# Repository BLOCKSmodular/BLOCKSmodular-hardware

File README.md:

# BLOCKSmodular-hardware
**WORK IN PROGRESS**  
This is work in progress. Please use it at your own risk.

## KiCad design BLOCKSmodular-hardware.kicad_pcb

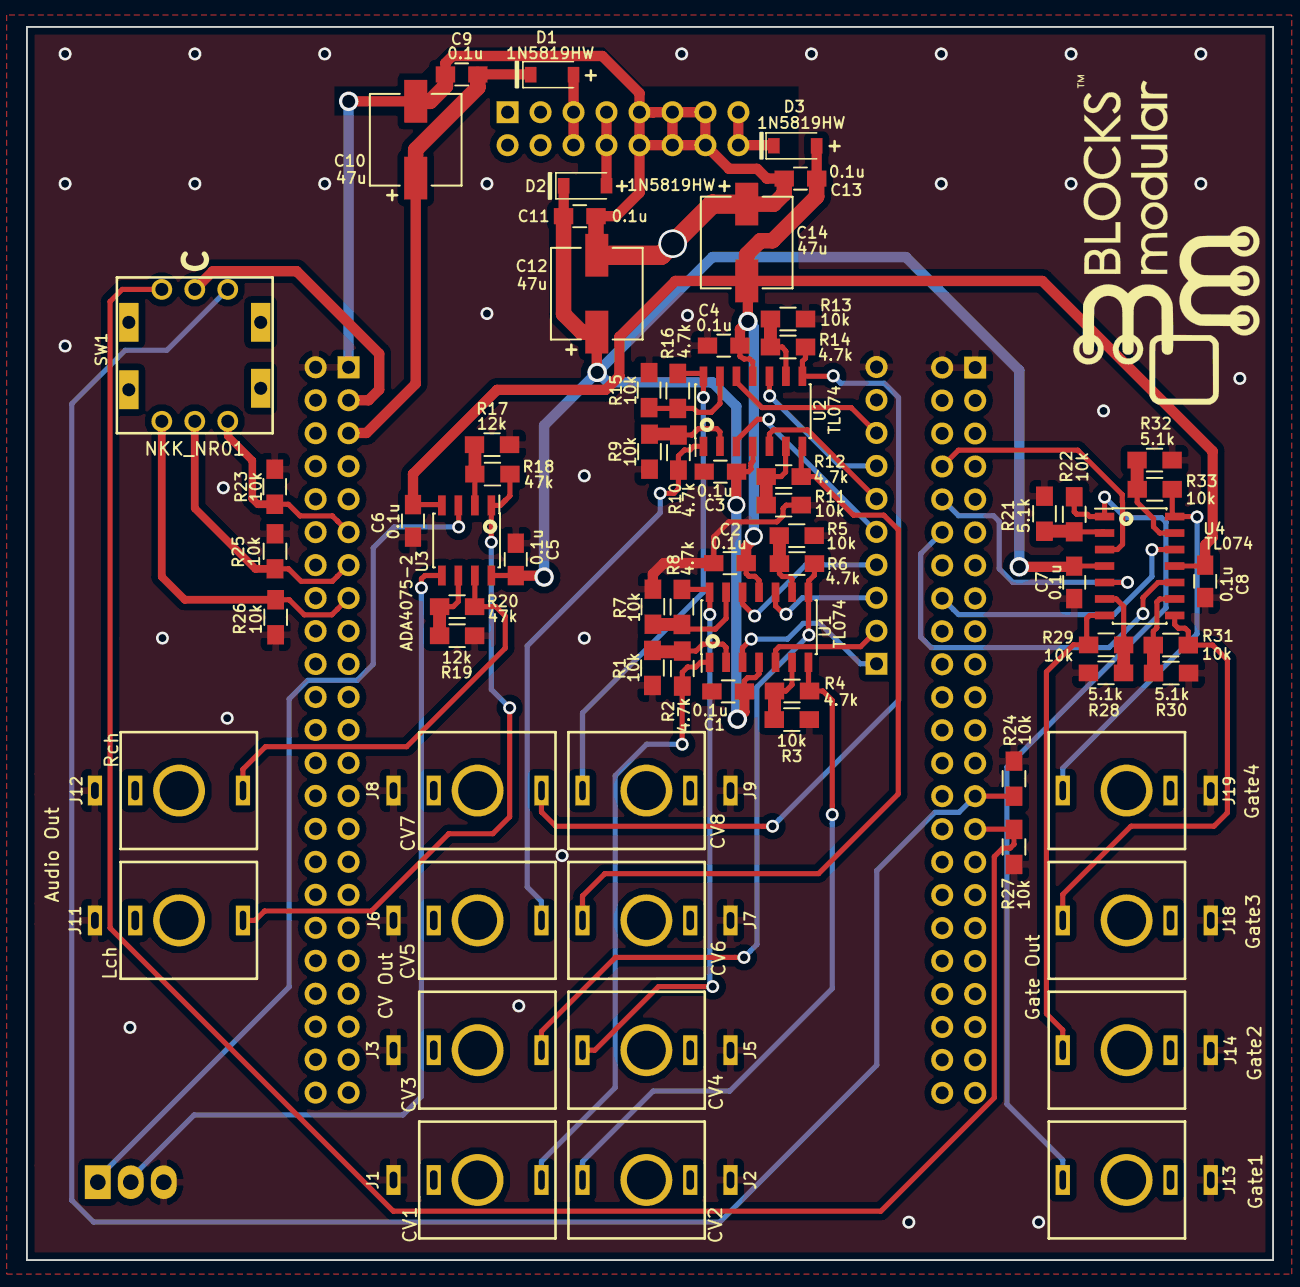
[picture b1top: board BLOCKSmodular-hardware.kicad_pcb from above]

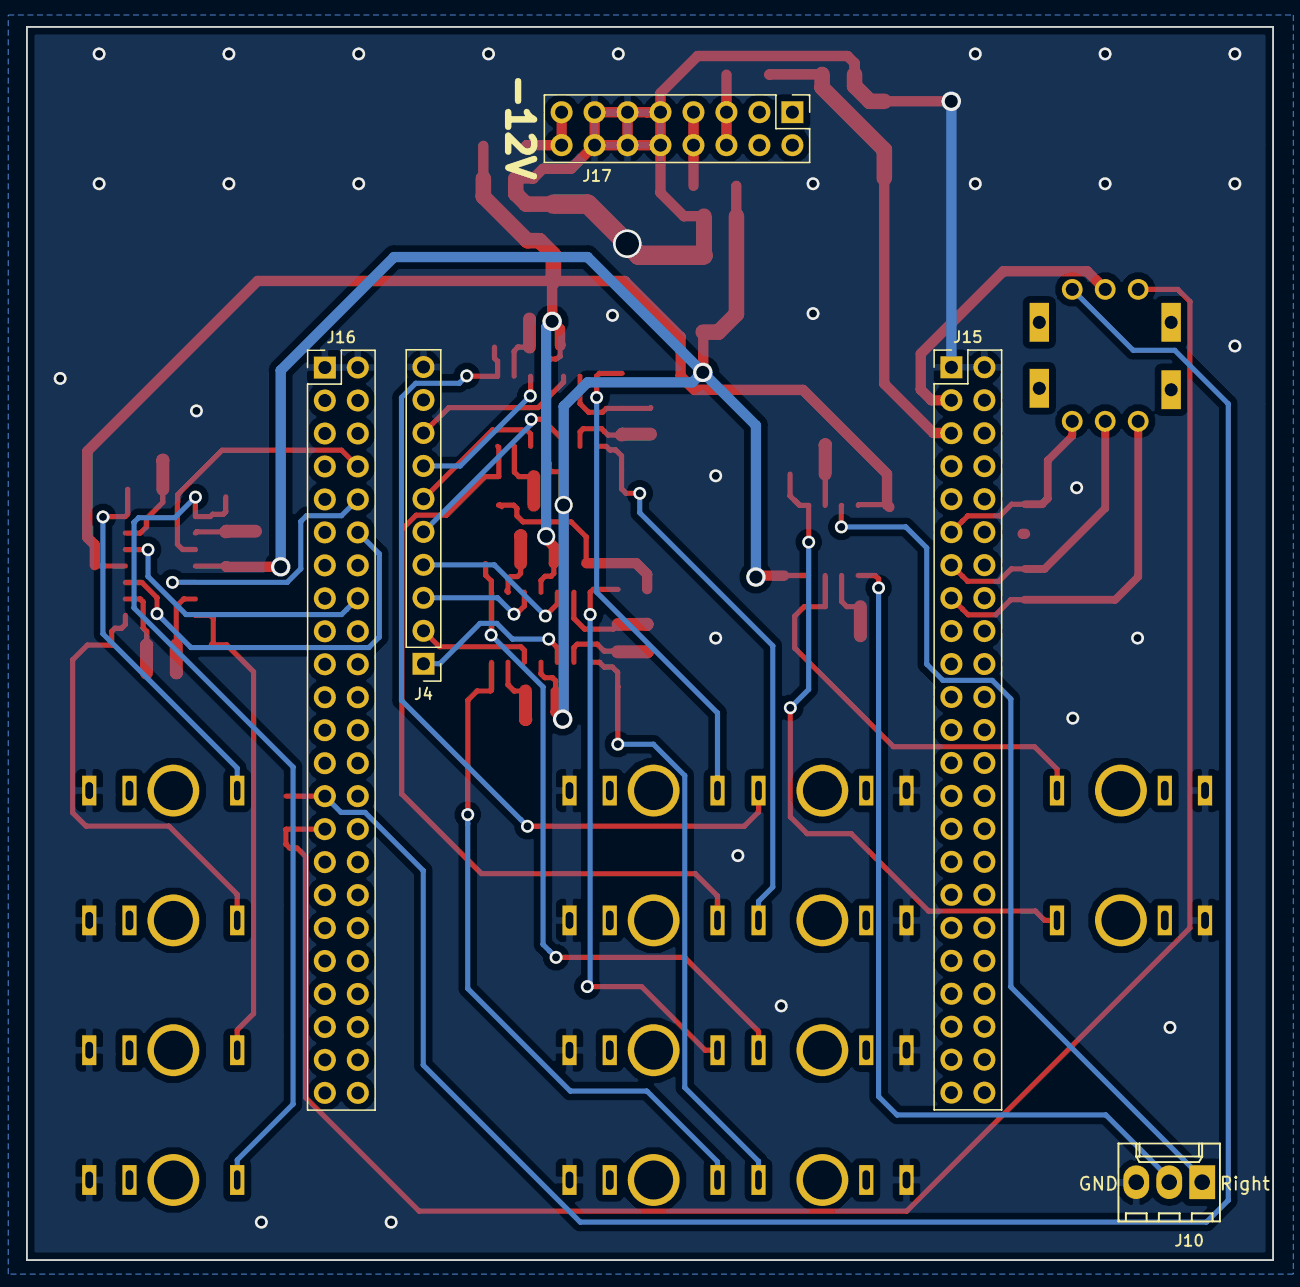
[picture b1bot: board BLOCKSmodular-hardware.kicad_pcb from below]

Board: 2 copper layers, 96.0 x 95.0 mm, 74 parts (5 on the bottom side), 55 nets.

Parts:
C1, C2, C3, C4, C5, C6, C7, C8, C9, C11, C13: 0.1u; C_0805_HandSoldering
C10, C12, C14: 47u; EEE-1VA470WP
D1, D2, D3: 1N5819HW; D_SOD-123
J1, J2, J3, J5, J6, J7, J8, J9, J11, J12, J13, J14, J18, J19: THONKICONN
J4: Bela_AnalogOut; Pin_Header_Straight_1x10_Pitch2.54mm
J10: Bela_AudioOut; Molex_KK-6410-03_03x2.54mm_Straight
J15: Bela_P9; Pin_Header_Straight_2x23_Pitch2.54mm
J16: Bela_P8; Pin_Header_Straight_2x23_Pitch2.54mm
J17: EurorackPower; Pin_Header_Straight_2x08_Pitch2.54mm
R1, R3, R5, R7, R9, R11, R13, R15, R22, R23, R24, R25, R26, R27, R29, R31, R33: 10k; R_0805_HandSoldering
R2, R4, R6, R8, R10, R12, R14, R16: 4.7k; R_0805_HandSoldering
R17, R19: 12k; R_0805_HandSoldering
R18, R20: 47k; R_0805_HandSoldering
R21, R28, R30, R32: 5.1k; R_0805_HandSoldering
SW1: NKK_NR01; NR01
U1, U2, U4: TL074; SOIC-14_3.9x8.7mm_Pitch1.27mm
U3: ADA4075-2; SOIC-8_3.9x4.9mm_Pitch1.27mm

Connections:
+5V: C9.1, C10.1, D1.1, J15.5
+12V: C1.2, C3.2, C5.2, C7.2, C11.1, C12.1, D2.1, U1.4, U2.4, U3.8, U4.4
-12V: C2.2, C4.2, C6.2, C8.2, C13.1, C14.2, D3.2, U1.11, U2.11, U3.4, U4.11
GND: C1.1, C2.1, C3.1, C4.1, C5.1, C6.1, C7.1, C8.1, C9.2, C10.2, C11.2, C12.2, C13.2, C14.1, J1.1, J2.1, J3.1, J4.10, J5.1, J6.1, J7.1, J8.1, J9.1, J10.3, J11.1, J12.1, J13.1, J14.1, J15.1, J15.2, J16.1, J16.2, J17.9, J17.10, J17.11, J17.12, J17.13, J17.14, J18.1, J19.1, R1.2, R3.2, R5.2, R7.2, R9.2, R11.2, R13.2, R15.2, R17.2, R19.2, R21.2, R23.1, R24.2, R25.1, R26.1, R27.1, R28.2, R30.2, R32.2
unnamed: D1.2, J17.5, J17.6
unnamed: D2.2, J17.7, J17.8
unnamed: D3.1, J17.15, J17.16
unnamed: J1.3, R2.1, U1.1
unnamed: J2.3, R4.1, U1.7
unnamed: J3.3, R6.1, U1.8
unnamed: J4.1, U1.3
unnamed: J4.2, U1.5
unnamed: J4.3, U1.10
unnamed: J4.4, U1.12
unnamed: J4.5, U2.3
unnamed: J4.6, U2.5
unnamed: J4.7, U2.10
unnamed: J4.8, U2.12
unnamed: J5.3, R8.1, U1.14
unnamed: J6.3, R10.1, U2.1
unnamed: J7.3, R12.1, U2.7
unnamed: J8.3, R14.1, U2.8
unnamed: J9.3, R16.1, U2.14
unnamed: J10.1, U3.3
unnamed: J10.2, U3.5
unnamed: J11.3, R18.1, U3.1
unnamed: J12.3, R20.1, U3.7
unnamed: J13.3, R22.1, U4.1
unnamed: J14.3, R29.1, U4.7
unnamed: J15.3, SW1.3
unnamed: J15.11, R23.2, SW1.2
unnamed: J15.13, R25.2, SW1.4
unnamed: J15.15, R26.2, SW1.6
unnamed: J16.8, U4.3
unnamed: J16.10, U4.5
unnamed: J16.12, U4.10
unnamed: J16.16, U4.12
unnamed: J16.27, R24.1, SW1.1
unnamed: J16.29, R27.2, SW1.5
unnamed: J18.3, R31.1, U4.8
unnamed: J19.3, R33.1, U4.14
unnamed: R1.1, R2.2, U1.2
unnamed: R3.1, R4.2, U1.6
unnamed: R5.1, R6.2, U1.9
unnamed: R7.1, R8.2, U1.13
unnamed: R9.1, R10.2, U2.2
unnamed: R11.1, R12.2, U2.6
unnamed: R13.1, R14.2, U2.9
unnamed: R15.1, R16.2, U2.13
unnamed: R17.1, R18.2, U3.2
unnamed: R19.1, R20.2, U3.6
unnamed: R21.1, R22.2, U4.2
unnamed: R28.1, R29.2, U4.6
unnamed: R30.1, R31.2, U4.9
unnamed: R32.1, R33.2, U4.13

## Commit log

2018-05-16 .gitignore
2018-05-16 Add: KiCadプロジェクトを追加
2018-05-25 Update: 基板修正
2018-05-25 Add: RevCのガーバーデータを追加。
2018-05-25 Add: KiCad用カスタムフットプリント とシンボルを追加
2018-05-25 Add: 寸法線を追加

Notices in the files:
parts and their libraries:
Copyright 2016 Accelerated Designs. All rights reserved.
